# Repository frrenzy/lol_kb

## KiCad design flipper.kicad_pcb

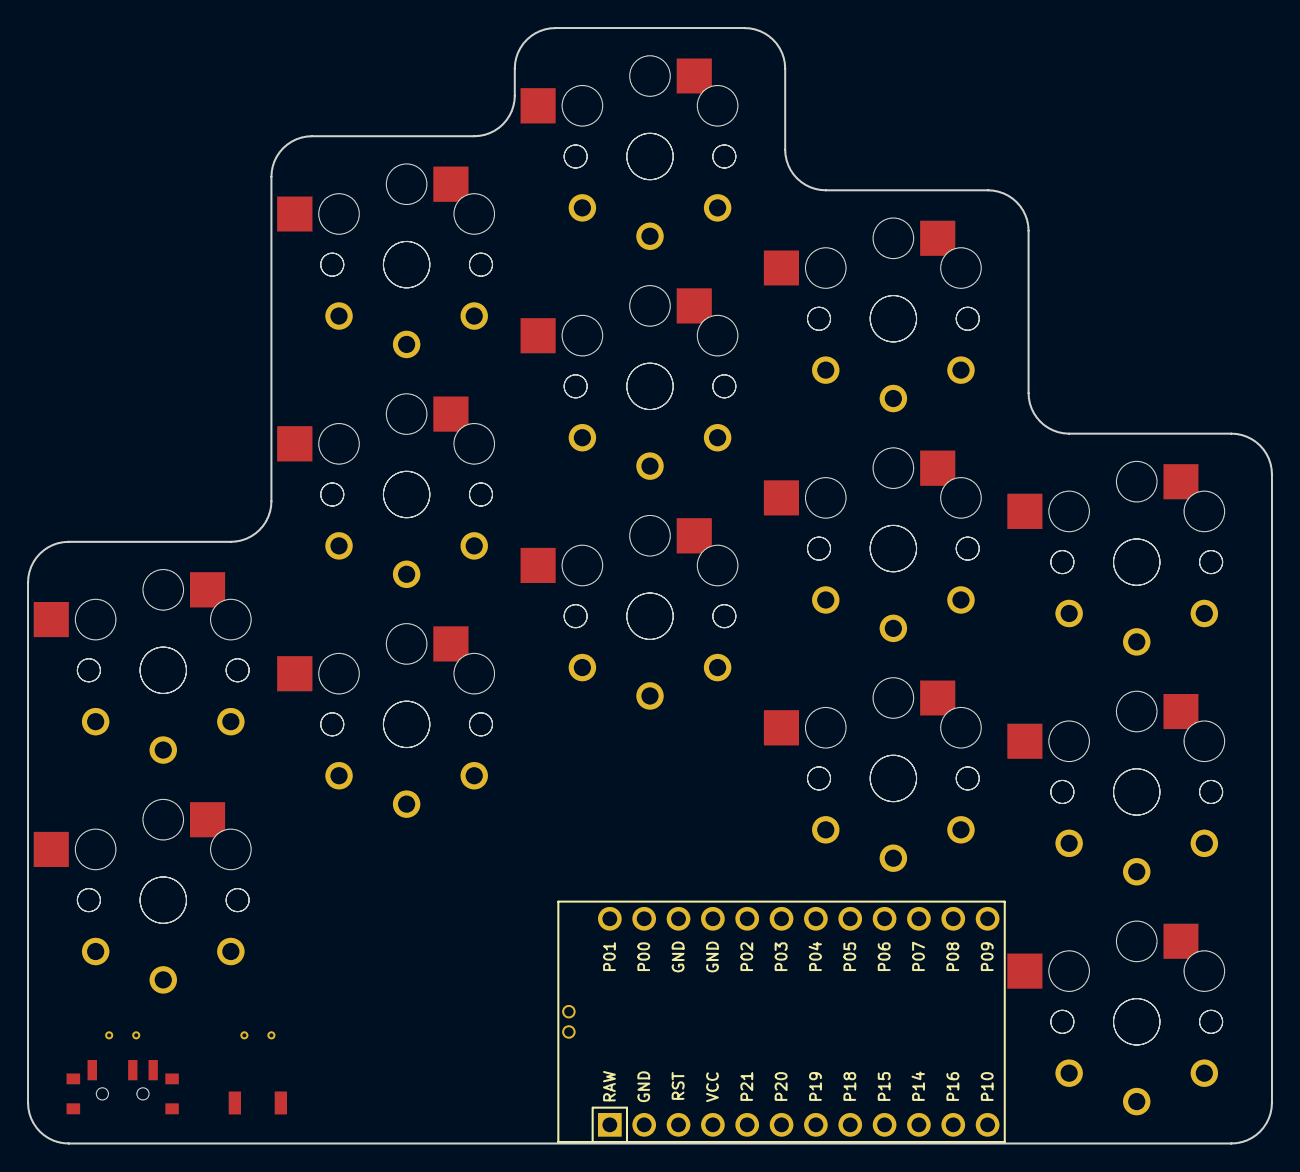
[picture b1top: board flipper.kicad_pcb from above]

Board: 2 copper layers, 92.0 x 82.5 mm, 29 parts (0 on the bottom side), 15 nets, no tracks yet.

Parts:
MCU1: ProMicro
S1, S2, S3, S4, S5, S6, S7, S8, S9, S10, S11, S12, S13, S14, S15, S16, S17, S18, S19, S20, S21, S22, S23, S24, S25, S26, S27, S28: PG1350

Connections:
GND: MCU1.2, MCU1.15, MCU1.16, S1.2, S2.2, S3.2, S4.2, S5.2, S6.2, S7.2, S8.2, S9.2, S10.2, S11.2, S12.2, S13.2, S14.2, S15.2, S16.2, S17.2, S18.2, S19.2, S20.2, S21.2, S22.2, S23.2, S24.2, S25.2, S26.2, S27.2, S28.2
P4: MCU1.19, S17.1, S18.1
P5: MCU1.20, S19.1, S20.1
P6: MCU1.21, S21.1, S22.1
P7: MCU1.22, S25.1, S26.1
P8: MCU1.23, S27.1, S28.1
P9: MCU1.24, S23.1, S24.1
P10: MCU1.12, S15.1, S16.1
P14: MCU1.10, S11.1, S12.1
P15: MCU1.9, S9.1, S10.1
P16: MCU1.11, S13.1, S14.1
P18: MCU1.8, S7.1, S8.1
P19: MCU1.7, S5.1, S6.1
P20: MCU1.6, S3.1, S4.1
P21: MCU1.5, S1.1, S2.1

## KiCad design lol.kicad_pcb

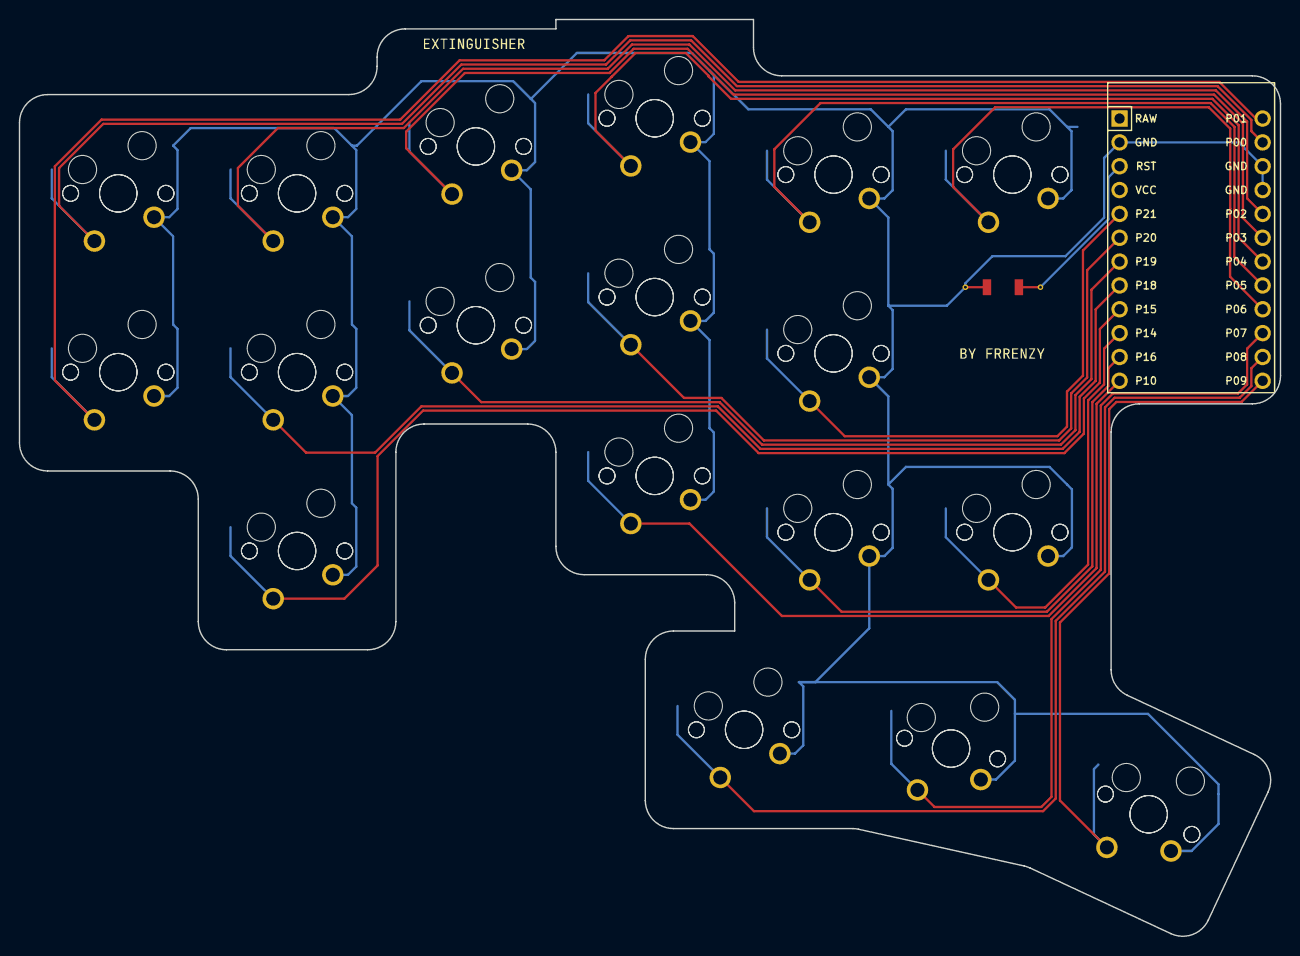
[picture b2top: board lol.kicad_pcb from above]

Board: 2 copper layers, 134.3 x 97.7 mm, 37 parts (0 on the bottom side), 19 nets.

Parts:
MCU1: ProMicro
S1, S2, S3, S4, S5, S6, S7, S8, S9, S10, S11, S12, S13, S14, S15, S16, S17, S18, S19, S20, S21, S22, S23, S24, S25, S26, S27, S28, S29, S30, S31, S32, S33, S34, S35, S36: MX

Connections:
GND: MCU1.2, MCU1.15, MCU1.16, S1.2, S2.2, S3.2, S4.2, S5.2, S6.2, S7.2, S8.2, S9.2, S10.2, S11.2, S12.2, S13.2, S14.2, S15.2, S16.2, S17.2, S18.2, S19.2, S20.2, S21.2, S22.2, S23.2, S24.2, S25.2, S26.2, S27.2, S28.2, S29.2, S30.2, S31.2, S32.2, S33.2, S34.2, S35.2, S36.2
P0: MCU1.14, S3.1, S4.1
P1: MCU1.13, S1.1, S2.1
P2: MCU1.17, S9.1, S10.1
P3: MCU1.18, S13.1, S14.1
P4: MCU1.19, S19.1, S20.1
P5: MCU1.20, S25.1, S26.1
P6: MCU1.21, S29.1, S30.1
P7: MCU1.22, S33.1, S34.1
P8: MCU1.23, S31.1, S32.1
P9: MCU1.24, S35.1, S36.1
P10: MCU1.12, S15.1, S16.1
P14: MCU1.10, S27.1, S28.1
P15: MCU1.9, S5.1, S6.1
P16: MCU1.11, S21.1, S22.1
P18: MCU1.8, S7.1, S8.1
P19: MCU1.7, S11.1, S12.1
P20: MCU1.6, S17.1, S18.1
P21: MCU1.5, S23.1, S24.1
